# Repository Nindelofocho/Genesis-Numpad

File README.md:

# Genesis Numpad
 Simple numpad with aesthetics

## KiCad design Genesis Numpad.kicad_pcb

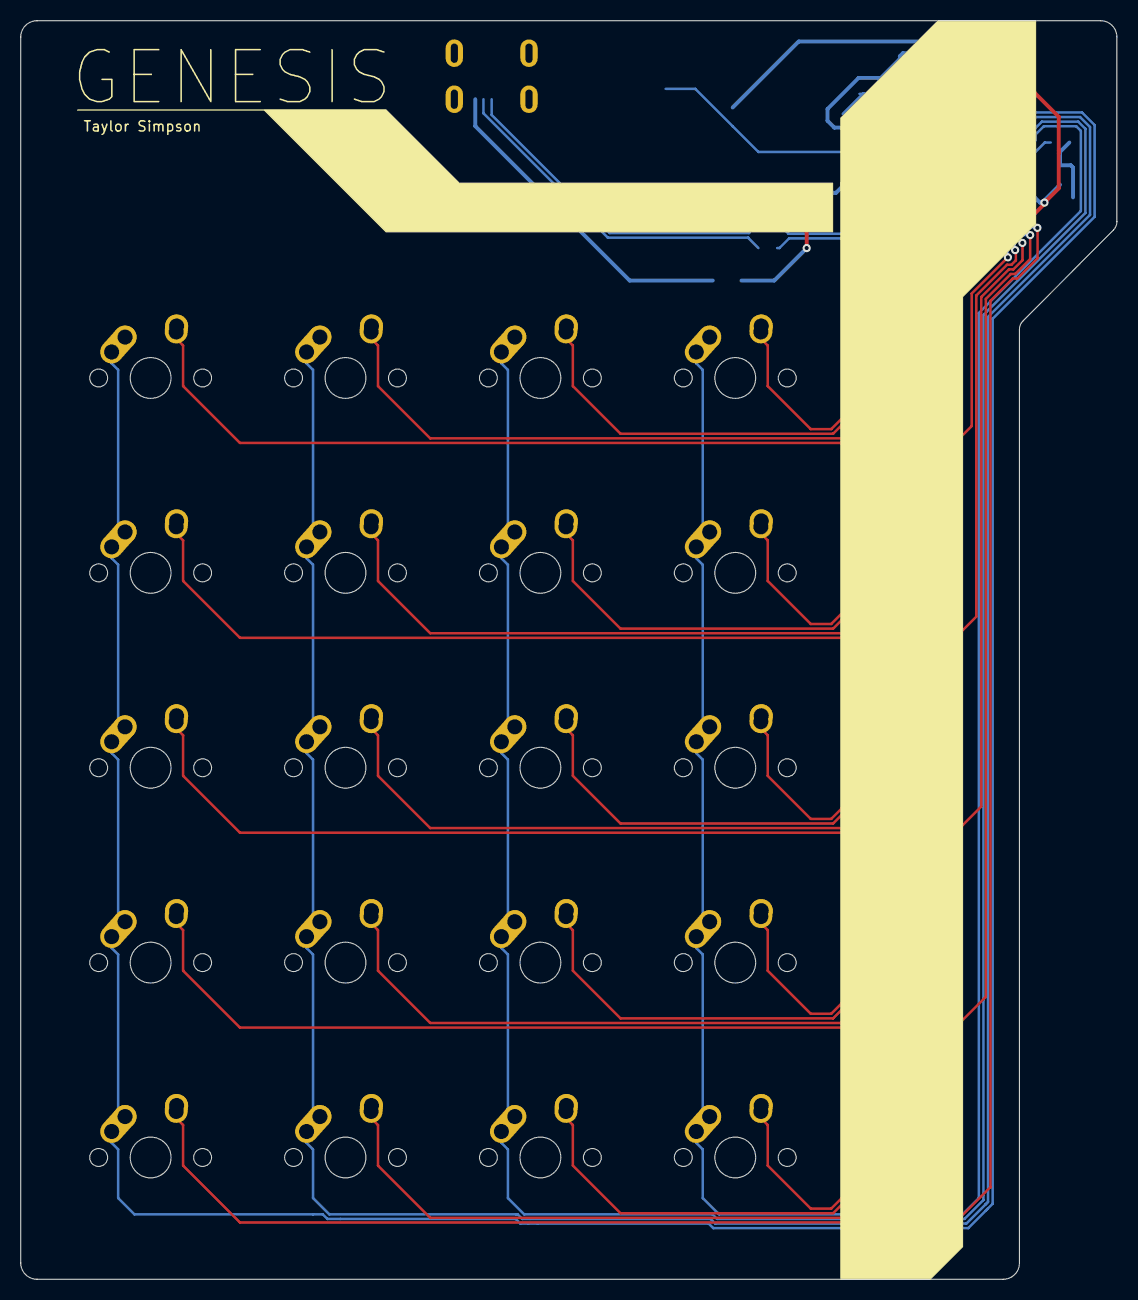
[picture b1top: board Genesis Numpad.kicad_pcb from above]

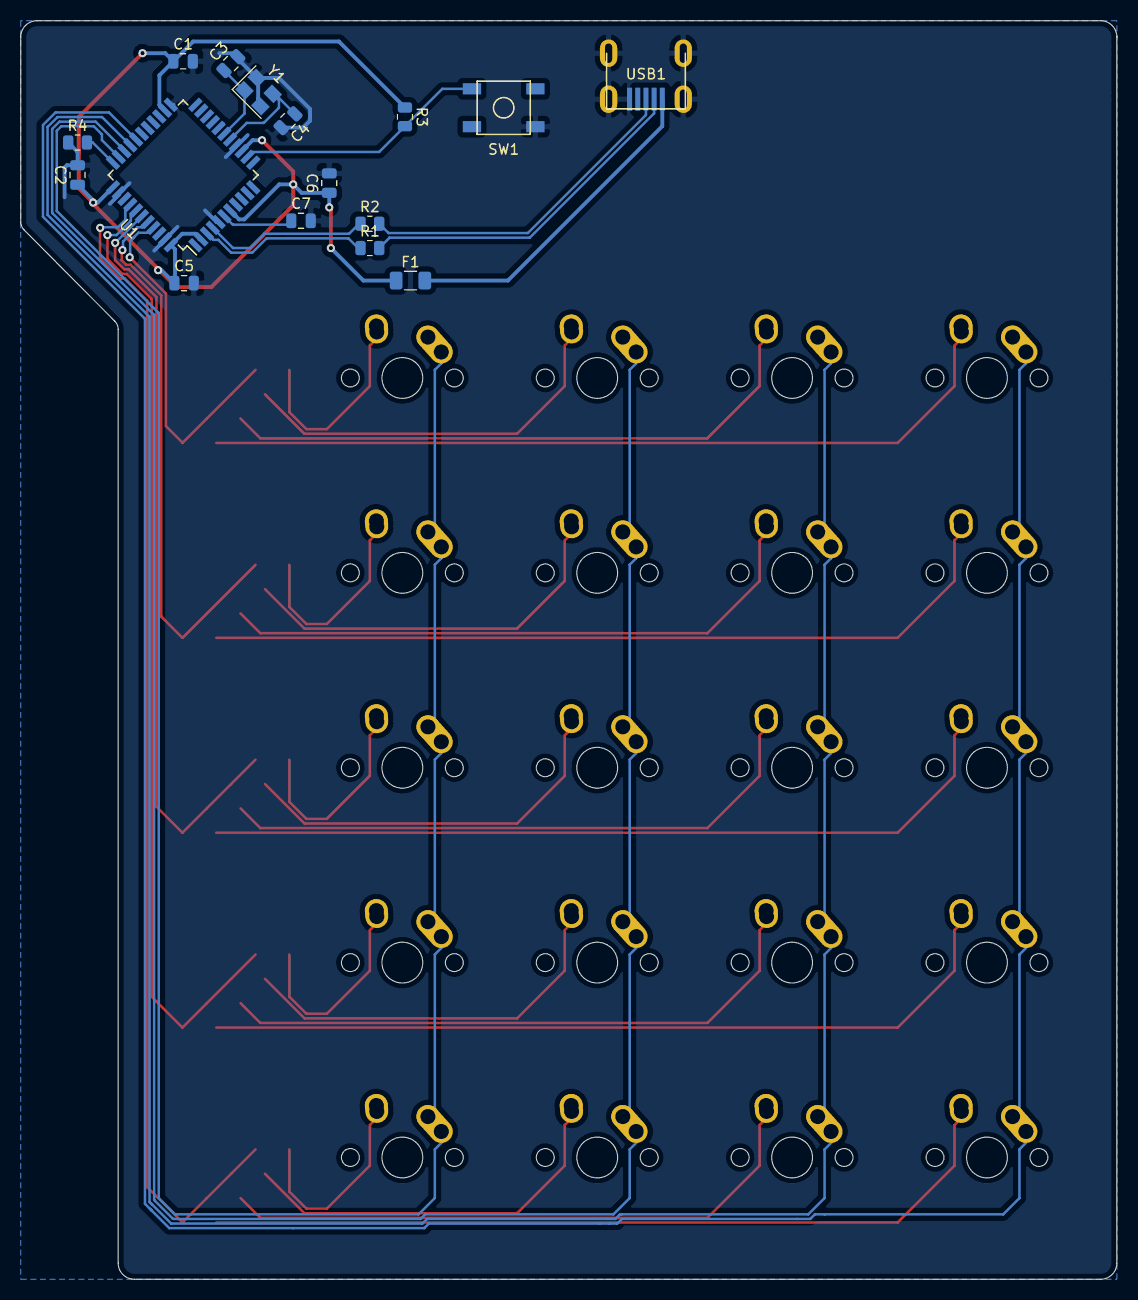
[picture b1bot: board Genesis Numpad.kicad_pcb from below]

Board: 2 copper layers, 107.2 x 123.0 mm, 56 parts (16 on the bottom side), 41 nets.

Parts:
C1, C2, C5: 0.1uF; C_0805_2012Metric
C3, C4: 22pF; C_0805_2012Metric
C6: 10uF; C_0805_2012Metric
C7: 1uF; C_0805_2012Metric
D1, D2, D3, D4, D5, D6, D7, D8, D9, D10, D11, D12, D13, D14, D15, D16, D17, D18, D19, D20: D_Small; D_SOD-123
F1: 500mA; Fuse_1206_3216Metric
MX1, MX2, MX3, MX4, MX5, MX6, MX7, MX8, MX9, MX10, MX11, MX12, MX13, MX14, MX15, MX16, MX17, MX18, MX19, MX20: MX-NoLED; MX-1U-NoLED
R1, R2: 22; R_0805_2012Metric
R3, R4: 10k; R_0805_2012Metric
SW1: SW_Push; SKQG-1155865
U1: ATmega32U4-AU; TQFP-44_10x10mm_P0.8mm
USB1: Molex-0548190589
Y1: 16MHz; Crystal_SMD_3225-4Pin_3.2x2.5mm

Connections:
+5V: C1.1, C2.1, C5.1, C6.1, F1.1, R3.1, U1.2, U1.7, U1.14, U1.24, U1.34, U1.44
COL0: MX1.1, MX2.1, MX3.1, MX4.1, MX5.1, U1.29
COL1: MX6.1, MX7.1, MX8.1, MX9.1, MX10.1, U1.30
COL2: MX11.1, MX12.1, MX13.1, MX14.1, MX15.1, U1.31
COL3: MX16.1, MX17.1, MX18.1, MX19.1, MX20.1, U1.32
D+: R2.2, USB1.3
D-: R1.2, USB1.4
GND: C1.2, C2.2, C3.2, C4.2, C5.2, C6.2, C7.2, R4.1, SW1.1, U1.5, U1.15, U1.23, U1.35, U1.43, USB1.1, USB1.6, Y1.2, Y1.4
unnamed: C3.1, U1.17, Y1.1
unnamed: C4.1, U1.16, Y1.3
unnamed: C7.1, U1.6
unnamed: D1.2, MX1.2
unnamed: D2.2, MX2.2
unnamed: D3.2, MX3.2
unnamed: D4.2, MX4.2
unnamed: D5.2, MX5.2
unnamed: D6.2, MX6.2
unnamed: D7.2, MX7.2
unnamed: D8.2, MX8.2
unnamed: D9.2, MX9.2
unnamed: D10.2, MX10.2
unnamed: D11.2, MX11.2
unnamed: D12.2, MX12.2
unnamed: D13.2, MX13.2
unnamed: D14.2, MX14.2
unnamed: D15.2, MX15.2
unnamed: D16.2, MX16.2
unnamed: D17.2, MX17.2
unnamed: D18.2, MX18.2
unnamed: D19.2, MX19.2
unnamed: D20.2, MX20.2
unnamed: R1.1, U1.3
unnamed: R2.1, U1.4
unnamed: R3.2, SW1.2, U1.13
unnamed: R4.2, U1.33
ROW0: D1.1, D6.1, D11.1, D16.1, U1.41
ROW1: D2.1, D7.1, D12.1, D17.1, U1.40
ROW2: D3.1, D8.1, D13.1, D18.1, U1.39
ROW3: D4.1, D9.1, D14.1, D19.1, U1.38
ROW4: D5.1, D10.1, D15.1, D20.1, U1.37
VCC: F1.2, USB1.5

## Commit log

2021-04-12 Project Initialization
2021-04-12 Add submodules
2021-04-12 Added Libraries
2021-04-12 Created Schematic
2021-04-12 Designed PCB
2021-04-12 Prettyfied board
2021-04-12 Added Default Layout Image
2021-04-12 Generated Gerbers
2021-04-12 Adjusted traces
2021-04-12 Unfricked some power lines
2021-04-12 Rerouted power
2021-04-13 Fixed Bugs
2021-04-13 Redraw ground plane
2021-04-13 Fixed Errors in design
